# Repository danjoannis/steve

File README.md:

# steve
Self-Training Electronic Vehicle for Exploration

STEVE is a fun little hobby project, combining an RC tank platform with a Raspberry Pi, Arduino Mega,
and plenty of sensors to allow him to discover the world.

The longterm goal is a robot which can autonomously navigate through environments in order to
reach assigned targets.

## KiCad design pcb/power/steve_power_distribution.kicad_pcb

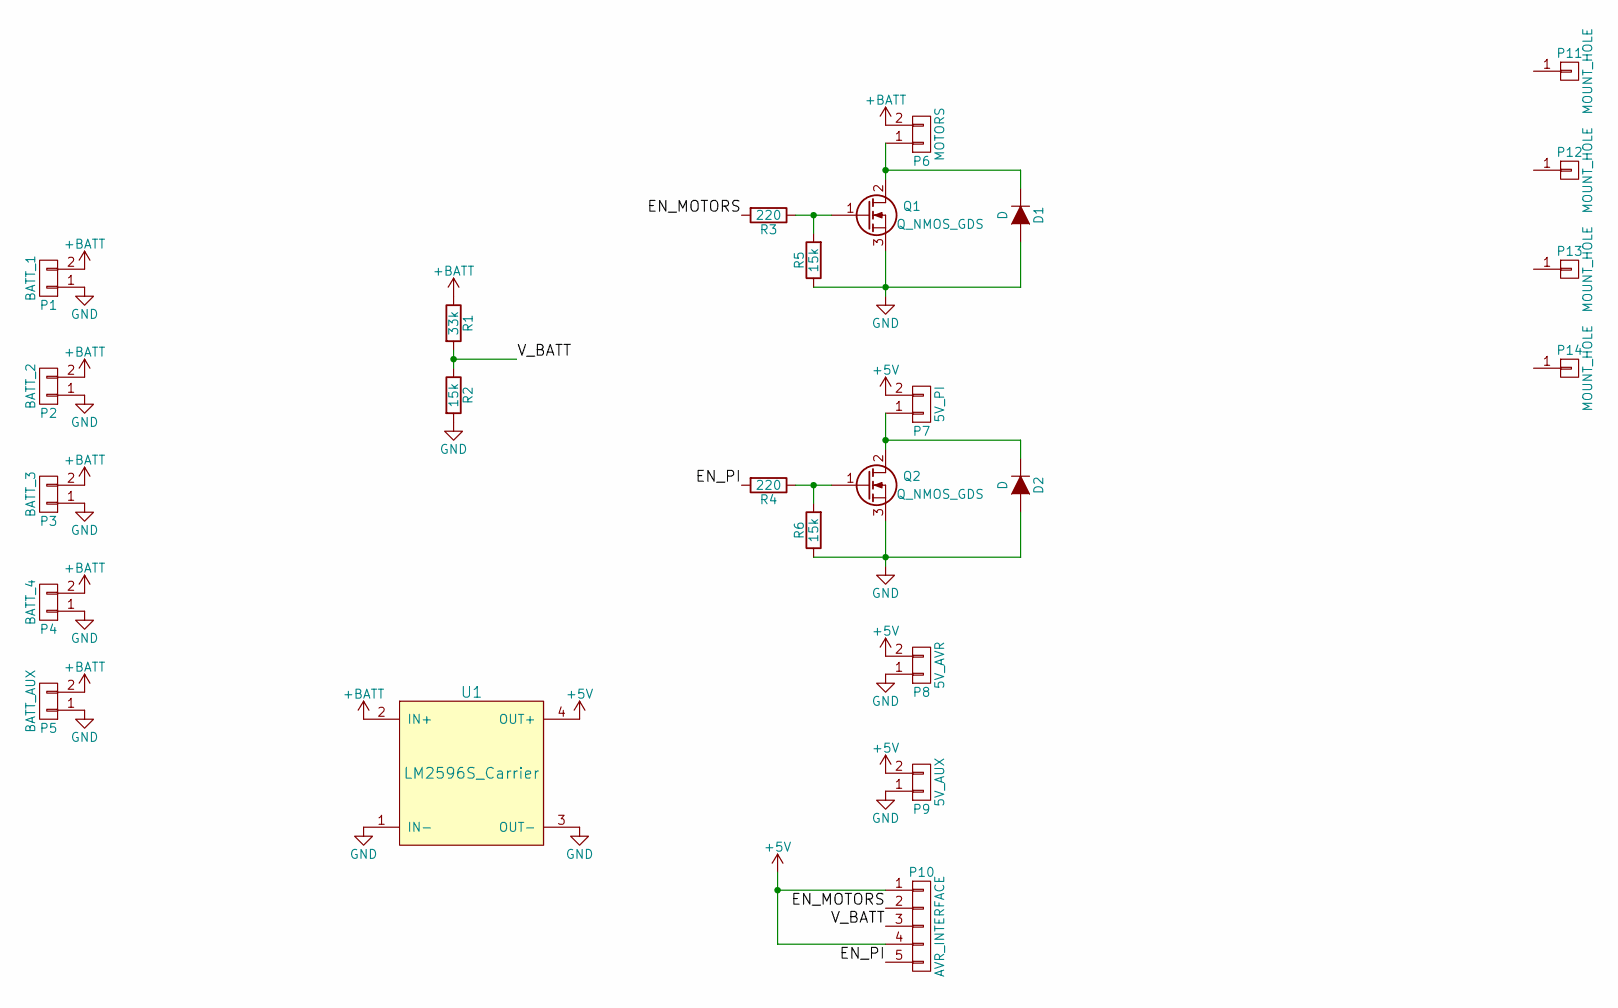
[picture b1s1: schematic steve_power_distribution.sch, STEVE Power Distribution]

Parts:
D1, D2: D; SMA_Handsoldering
P1: BATT_1; TerminalBlock_Pheonix_PT-3.5mm_2pol
P2: BATT_2; TerminalBlock_Pheonix_PT-3.5mm_2pol
P3: BATT_3; TerminalBlock_Pheonix_PT-3.5mm_2pol
P4: BATT_4; TerminalBlock_Pheonix_PT-3.5mm_2pol
P5: BATT_AUX; TerminalBlock_Pheonix_PT-3.5mm_2pol
P6: MOTORS; TerminalBlock_Pheonix_PT-3.5mm_2pol
P7: 5V_PI; TerminalBlock_Pheonix_PT-3.5mm_2pol
P8: 5V_AVR; TerminalBlock_Pheonix_PT-3.5mm_2pol
P9: 5V_AUX; TerminalBlock_Pheonix_PT-3.5mm_2pol
P10: AVR_INTERFACE; Pin_Header_Straight_1x05
P11, P12, P13, P14: MOUNT_HOLE
Q1, Q2: Q_NMOS_GDS; TO-252-2Lead
R1: 33k; Resistor_Horizontal_RM10mm
R2, R5, R6: 15k; Resistor_Horizontal_RM10mm
R3, R4: 220; Resistor_Horizontal_RM10mm
U1: LM2596S_Carrier; LM2596S_CARRIER

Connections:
+5V: P7.2, P8.2, P9.2, P10.1, P10.4, U1.4 (OUT+)
+BATT: P1.2, P2.2, P3.2, P4.2, P5.2, P6.2, R1.1, U1.2 (IN+)
/EN_MOTORS: P10.2, R3.2
/EN_PI: P10.5, R4.2
/V_BATT: P10.3, R1.2, R2.1
GND: D1.2 (A), D2.2 (A), P1.1, P2.1, P3.1, P4.1, P5.1, P8.1, P9.1, Q1.3 (S), Q2.3 (S), R2.2, R5.1, R6.1, U1.1 (IN-), U1.3 (OUT-)
unnamed: D1.1 (K), P6.1, Q1.2 (D)
unnamed: D2.1 (K), P7.1, Q2.2 (D)
unnamed: Q1.1 (G), R3.1, R5.2
unnamed: Q2.1 (G), R4.1, R6.2

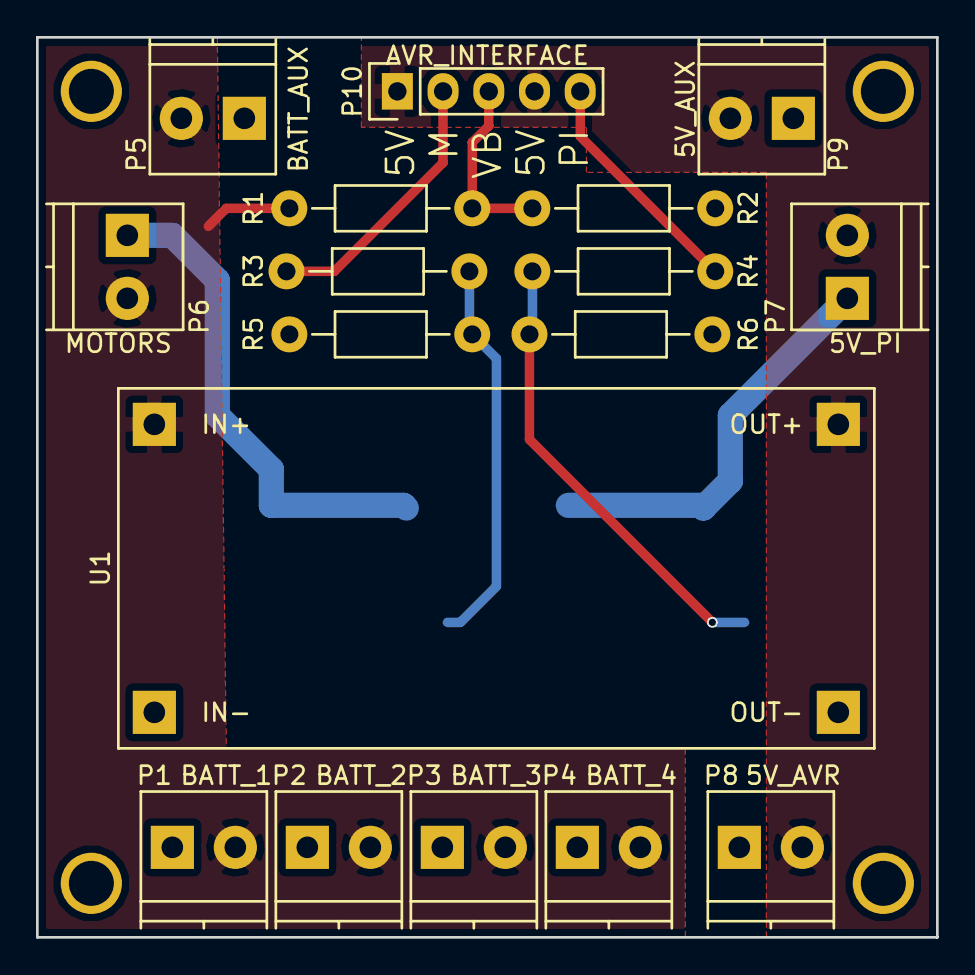
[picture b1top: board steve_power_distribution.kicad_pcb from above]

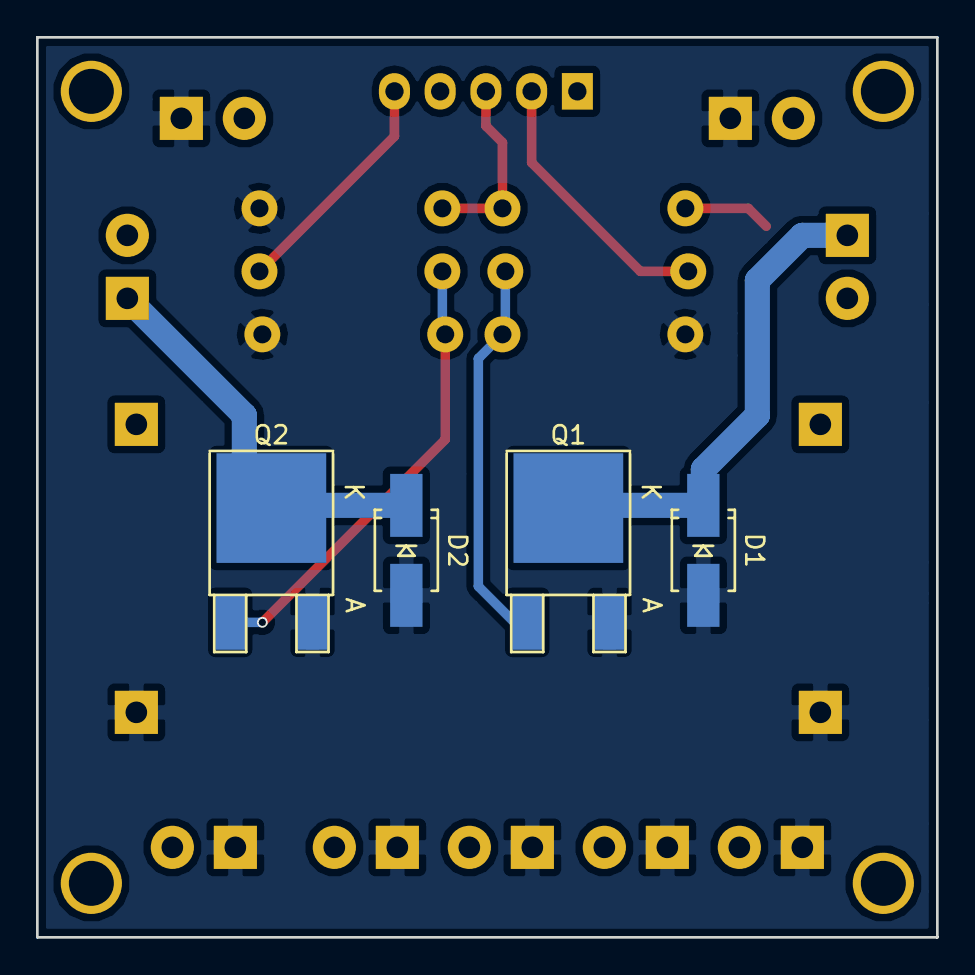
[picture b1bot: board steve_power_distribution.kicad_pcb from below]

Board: 2 copper layers, 50.0 x 50.0 mm, 25 parts (4 on the bottom side), 10 nets.

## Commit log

2015-12-06 Real initial commit
    Initial commit of all source code, 3D files, and documentation developed
    to date.
2015-12-06 First python bits for connecting with Arduino
2015-12-06 Added basic python logging script Improved serial connection file
2015-12-12 Created 3d model for LM298 holder
2015-12-12 Updated burnout function
2015-12-12 New build with burnout
2015-12-12 Fixed compile
2015-12-12 Initial commit of Linux application
2015-12-12 Added serial library
2015-12-12 Added serial header
2015-12-12 Modified serial library for arduino
2015-12-12 Updated serial libs and python scripts
2015-12-12 Moved around header includes for serial
2015-12-13 Fixes to allow compiling, due to printf
2015-12-13 More fixes
2015-12-13 New RS-232 library
2015-12-13 Stuff and doc
2016-03-20 Moved to Arduino platform
    Library support for AVR is pretty sad; switched it all to Arduino for
    better PWM and etc support.
    Renamed old code to arduino_io_legacy
2016-03-20 Change to .cpp file that likely wont be used
2016-03-20 Fixed MPU retrig
2016-03-21 Update documentation
2016-03-21 Updated drive dynamics
2016-03-21 Added old pythong code thing
2016-03-21 Updated motor dynamics (again); need to change pin assignment.
2016-03-22 Added pinout document
2016-03-22 Actually fixed motor pinout and stuff
2016-03-22 Updated pinout document
2016-03-31 Updated setup instructions
2016-03-31 More setup updates
2016-09-10 Changed pinout for Mega 2560
2016-09-10 Added new pinout document for Mega
2016-09-10 Created legacy folder, updated readme
2016-09-11 Initial PCB schematic capture and KiCAD project
2016-09-11 Added initial python webui files
2016-09-11 Testing main html changes
2016-09-11 Refined main console page
2016-09-11 Fixed embed bug maybe
2016-09-11 HTML fix using w3 schools helper
2016-09-11 Updated script to included cpu temp and time handlers
2016-09-11 Added javascript polling
2016-09-11 Better polling
2016-09-11 Added serial interface to web server, fixed baud rate
2016-09-11 Added measurement for front range finder
2016-09-11 Made divs inline, modified polling function
2016-09-11 Fix for div inline
2016-09-11 Fixed infinite function loop
2016-09-11 Ugh.. javascript sucks
2016-09-12 Semi finalized PCB layout
2016-09-12 Finally have driving from web UI working. Also added a "warehouse" module for stats
2016-09-12 Missing semi colon, missing quotes
2016-09-12 Steve lives and drives, improved
2016-09-12 Removed unneeded pyc file
2016-09-13 Finalized PCB design and generated gerbers for manufacture
2016-09-14 Added error handling for serial connection and Steve voice
2016-09-14 Break was unneeded
2016-09-14 Added voice prompts
2016-09-14 Made bottle run as a process maybe
2016-09-14 Fixed process running maybe
2016-09-14 Reverted process attempts
2016-09-14 Fixed joystick bug for duty - now uses pythagorus to get absolute magnitude
2016-09-14 Why does word do this...
2016-09-29 New box 3d part
2016-09-29 Updated pinout and BOM for PCB
2016-09-30 Updated electronics box, added grill, updated pinout, added code for power board
2016-10-03 Updated web interface and python script for stability; disabled warehouse; added remote IP setting
2016-10-03 Updated setup document
2016-10-03 Improved battery voltage function
2016-10-04 Improved (maybe) motor controls, added power management functions
2016-10-04 Added startup script and made dedicated dyanic IP updater
2016-10-04 Added IP watchdog process and a poweroff method
2016-10-07 Many real life code improvements, added more web ui controls, improved start up script, improved ip watchdog
2017-04-15 New 3D model for widening body
2017-05-09 Developing Android Server Application
2018-01-08 Android app mods
